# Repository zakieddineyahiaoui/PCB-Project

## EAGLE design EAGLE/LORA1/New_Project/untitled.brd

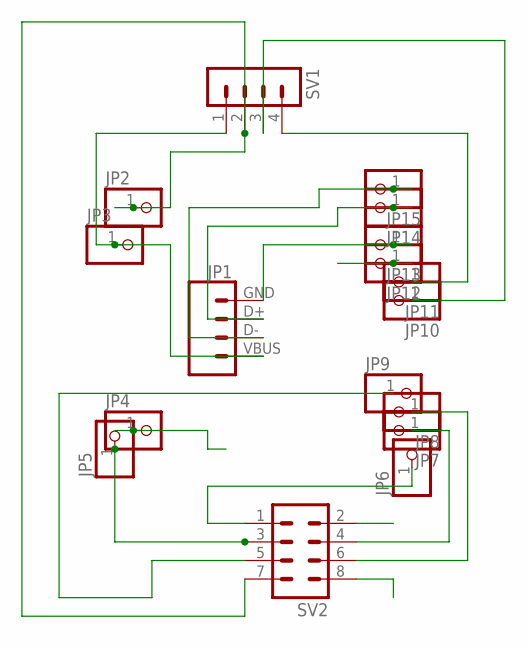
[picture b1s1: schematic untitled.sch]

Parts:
JP1: USB_SOLDER_PADS; USB-SOLDER-PADS
JP2, JP3, JP4, JP5, JP6, JP7, JP8, JP9, JP10, JP11, JP12, JP13, JP14, JP15: PINHD-1X1; 1X01
SV1: MA04-1
SV2: MA04-2

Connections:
unnamed: JP1.VBUS (1), JP3.1, SV1.1
unnamed: JP1.GND (4), JP13.1
unnamed: JP11.1, SV1.4
unnamed: JP10.1, SV1.3
unnamed: JP8.1, SV2.6
unnamed: JP1.D+ (3), JP14.1
unnamed: JP1.D- (2), JP15.1
unnamed: JP5.1, SV2.3
unnamed: JP6.1, SV2.1
unnamed: JP7.1, SV2.4
unnamed: JP2.1, SV1.2, SV2.7
unnamed: JP9.1, SV2.5

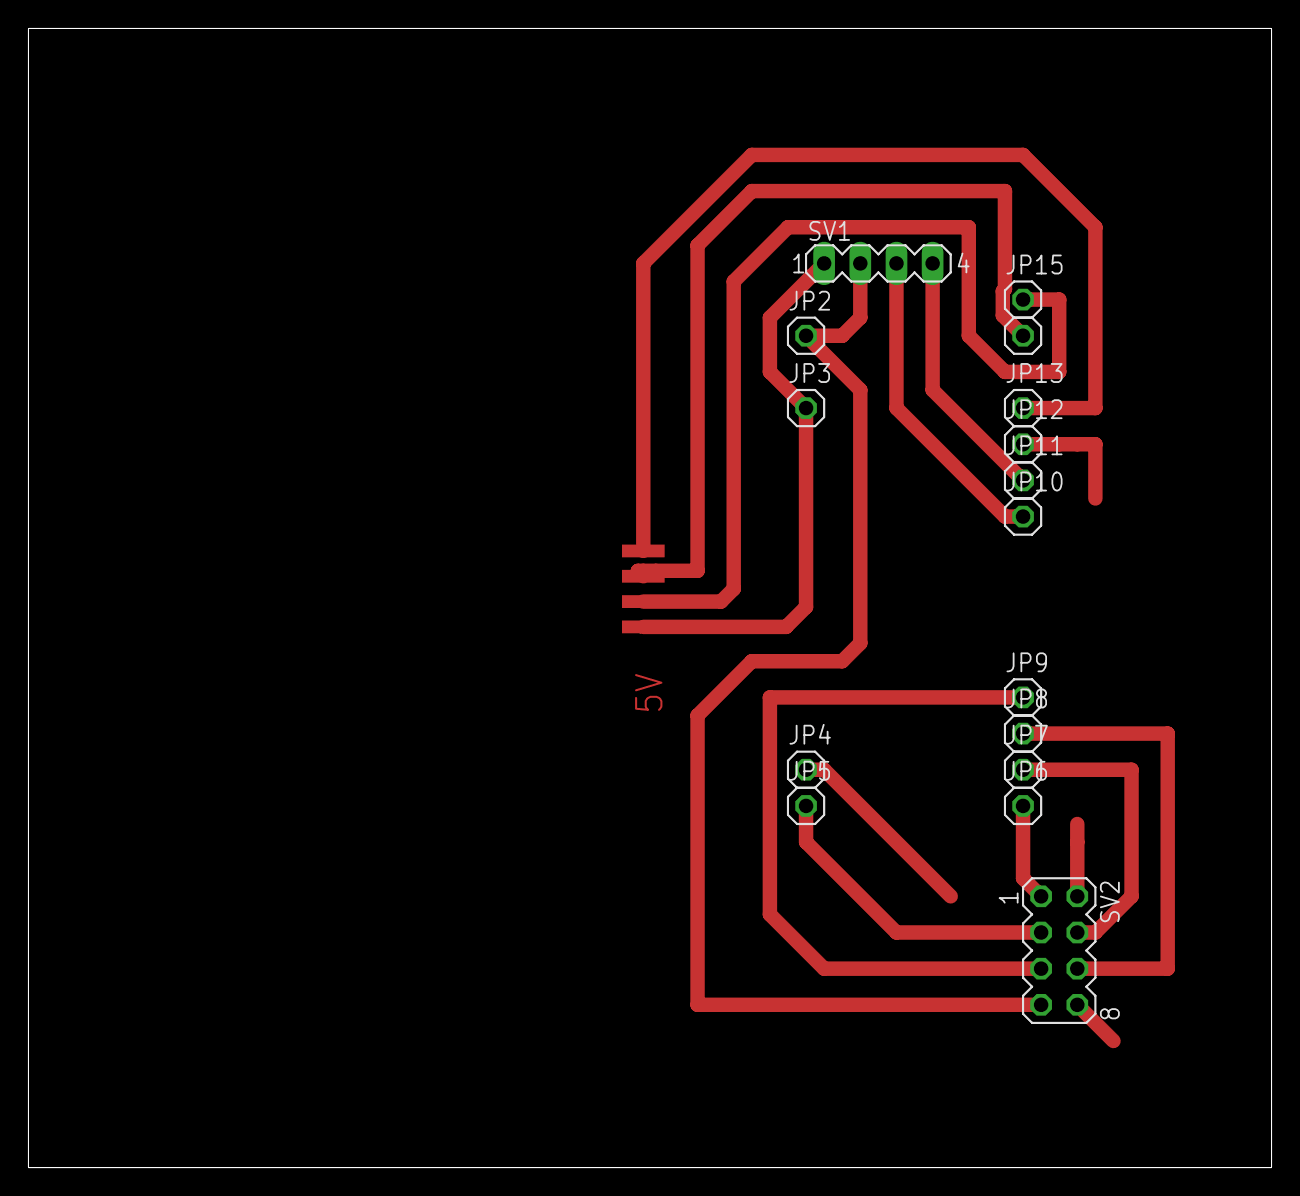
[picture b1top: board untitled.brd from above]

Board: 2 copper layers, 87.3 x 80.0 mm, 17 parts (0 on the bottom side), 12 nets.

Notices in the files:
parts and their libraries:
SparkFun-Connectors: Licensing: Creative Commons ShareAlike 4.0 International - https://creativecommons.org/licenses/by-sa/4.0
